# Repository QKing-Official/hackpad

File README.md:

# hackpad
My design for Blueprints HackPad and my first PCB!

I have designed my own design of the HackPad.
I have placed 6 switches, each wired to it's own GPIO pin so it's easier to work with it software-wise.
I have carefully read the pinout for the rp2040 and based my connection on the support each pin has.
This PCB is focussed on software support, since I love that part the most.
I also added an 4 pin male header to later connect the OLED display to the HackPad.
This oled display will be used for various types of data.
Since I focussed this PCB on software I also chained the RGB-LED's to each other since they would otherwise take up all other pins.
Since they should be iduvidually controllable, this is no issue.
I have properly grounded the PCB using groundplains to ensure proper functionality.
I have tried to size the PCB properly, but this might have been an issue. Its ~87.25mm x 56.24mm.
The case that I designed is small and ensures proper acces to all io.

NOTE:

I tried my best, but this is my first PCB. So if there are any issues please tell them and I will try to solve them.

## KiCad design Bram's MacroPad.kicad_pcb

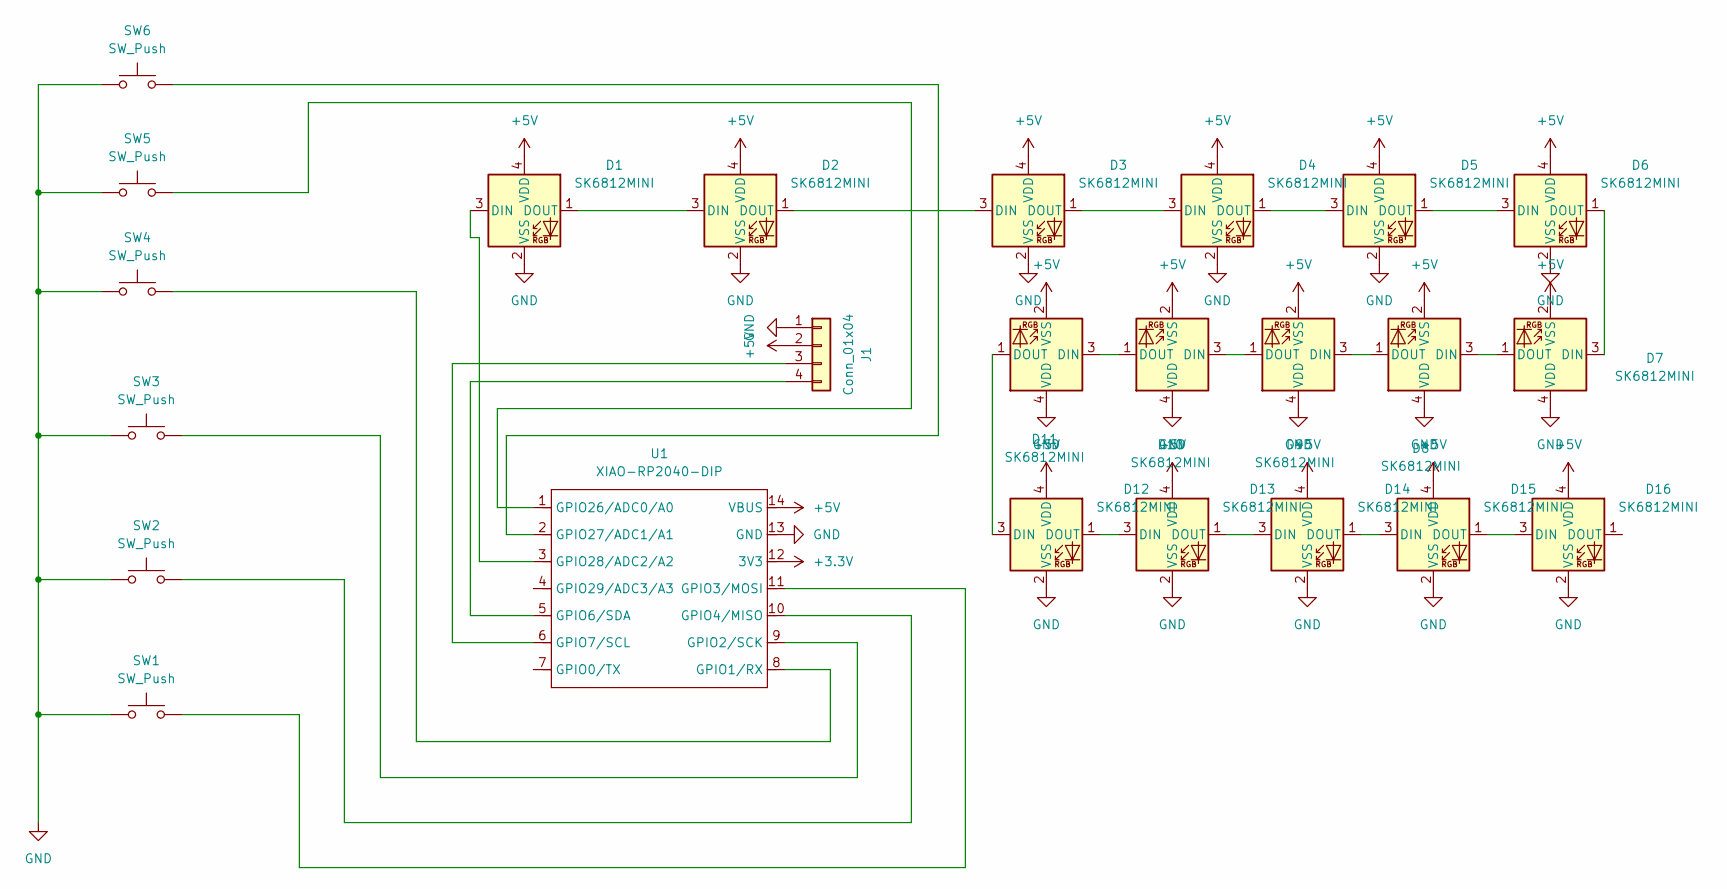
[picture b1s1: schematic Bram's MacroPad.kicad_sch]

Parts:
D1, D2, D3, D4, D5, D6, D7, D8, D9, D10, D11, D12, D13, D14, D15, D16: SK6812MINI; LED_SK6812MINI_PLCC4_3.5x3.5mm_P1.75mm
J1: Conn_01x04; SSD1306-0.91-OLED-4pin-128x32
SW1, SW2, SW3, SW4, SW5, SW6: SW_Push; SW_Cherry_MX_1.00u_PCB
U1: XIAO-RP2040-DIP

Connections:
+3.3V: U1.12 (3V3)
+5V: D1.4 (VDD), D2.4 (VDD), D3.4 (VDD), D4.4 (VDD), D5.4 (VDD), D6.4 (VDD), D7.2 (VSS), D8.2 (VSS), D9.2 (VSS), D10.2 (VSS), D11.2 (VSS), D12.4 (VDD), D13.4 (VDD), D14.4 (VDD), D15.4 (VDD), D16.4 (VDD), J1.2, U1.14 (VBUS)
GND: D1.2 (VSS), D2.2 (VSS), D3.2 (VSS), D4.2 (VSS), D5.2 (VSS), D6.2 (VSS), D7.4 (VDD), D8.4 (VDD), D9.4 (VDD), D10.4 (VDD), D11.4 (VDD), D12.2 (VSS), D13.2 (VSS), D14.2 (VSS), D15.2 (VSS), D16.2 (VSS), J1.1, SW1.1, SW2.1, SW3.1, SW4.1, SW5.1, SW6.1, U1.13 (GND)
unnamed: D1.3 (DIN), U1.3 (GPIO28/ADC2/A2)
unnamed: D1.1 (DOUT), D2.3 (DIN)
unnamed: D2.1 (DOUT), D3.3 (DIN)
unnamed: D3.1 (DOUT), D4.3 (DIN)
unnamed: D4.1 (DOUT), D5.3 (DIN)
unnamed: D5.1 (DOUT), D6.3 (DIN)
unnamed: D6.1 (DOUT), D7.3 (DIN)
unnamed: D7.1 (DOUT), D8.3 (DIN)
unnamed: D8.1 (DOUT), D9.3 (DIN)
unnamed: D9.1 (DOUT), D10.3 (DIN)
unnamed: D10.1 (DOUT), D11.3 (DIN)
unnamed: D11.1 (DOUT), D12.3 (DIN)
unnamed: D12.1 (DOUT), D13.3 (DIN)
unnamed: D13.1 (DOUT), D14.3 (DIN)
unnamed: D14.1 (DOUT), D15.3 (DIN)
unnamed: D15.1 (DOUT), D16.3 (DIN)
unnamed: J1.3, U1.6 (GPIO7/SCL)
unnamed: J1.4, U1.5 (GPIO6/SDA)
unnamed: SW4.2, U1.8 (GPIO1/RX)
unnamed: SW3.2, U1.9 (GPIO2/SCK)
unnamed: SW1.2, U1.11 (GPIO3/MOSI)
unnamed: SW2.2, U1.10 (GPIO4/MISO)
unnamed: SW5.2, U1.1 (GPIO26/ADC0/A0)
unnamed: SW6.2, U1.2 (GPIO27/ADC1/A1)

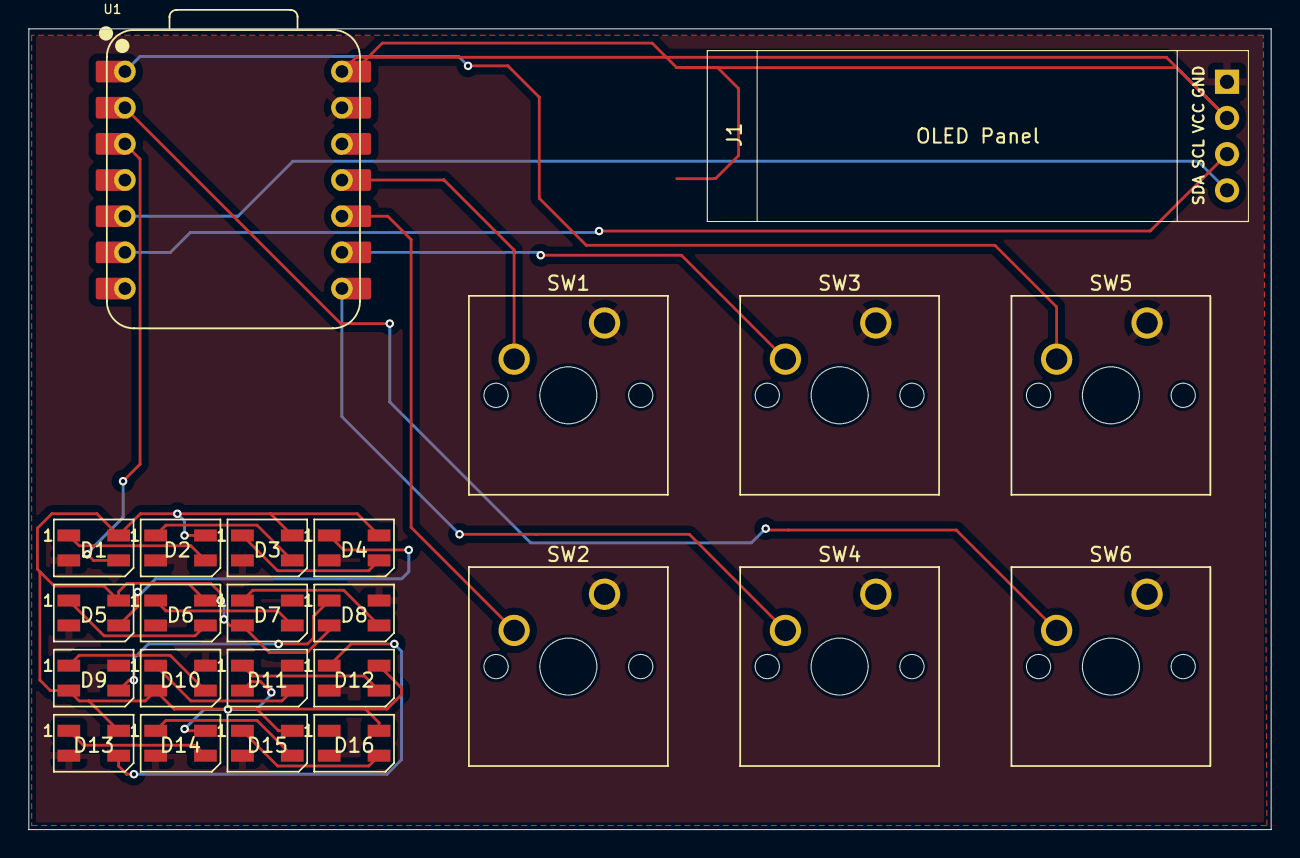
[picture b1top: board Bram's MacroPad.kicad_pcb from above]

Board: 2 copper layers, 87.2 x 56.2 mm, 24 parts (0 on the bottom side), 26 nets.

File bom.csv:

Designator,Footprint,Quantity,Value,LCSC Part #
"D1, D2, D3, D4, D5, D6, D7, D8, D9, D10, D11, D12, D13, D14, D15, D16",LED_SMD:LED_SK6812MINI_PLCC4_3.5x3.5mm_P1.75mm,16,SK6812MINI,
"SW1, SW2, SW3, SW4, SW5, SW6",Button_Switch_Keyboard:SW_Cherry_MX_1.00u_PCB,6,SW_Push,
U1,OPL_Xiao:XIAO-RP2040-DIP,1,XIAO-RP2040-DIP,
J1,0.91_OLED_display:SSD1306-0.91-OLED-4pin-128x32,1,Conn_01x04,
"SW1, SW2, SW3, SW4, SW5, SW6 (Keycaps)",Keycap_MX_1u,6,Keycap_1u,

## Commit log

2026-03-31 Rename Schermafbeelding 2026-03-31 191309.png to case.png
2026-03-31 Rename Schermafbeelding 2026-03-31 191335.png to pcb.png
